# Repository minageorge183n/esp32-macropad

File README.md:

# 🔘 ESP32 Bluetooth + WiFi Macropad

A custom-built macropad featuring **9 programmable keys** and **2 rotary encoders**, designed for productivity, streaming, editing, and general automation.
It connects via **Bluetooth** for real-time input and **WiFi** for easy configuration through a web-based UI.

---

## ✨ Features

* 🎹 **9 Mechanical Keys**
  Fully programmable keys that can send:

  * Keyboard shortcuts
  * Media controls
  * Text strings

* 🔄 **2 Rotary Encoders**
  Each encoder supports:

  * Clockwise / Counterclockwise rotation
  * Push button click

* 📡 **Dual Connectivity**

  * **Bluetooth (BLE)** → Acts as a wireless keyboard
  * **WiFi** → Hosts a configuration web interface

* 🌐 **Web UI Configuration**

  * Access via browser (phone or PC)
  * Remap keys and encoders 
  * No need to reflash firmware for changes

---

## ⚙️ How It Works

### Bluetooth Mode

* The macropad connects to your device as a **BLE keyboard**
* Pressing keys sends predefined actions instantly

### WiFi Mode

* The device creates or connects to a WiFi network
* You access a **local web page** hosted on the ESP32
* From there, you can:

  * Change key mappings
  * Assign new actions
  * Save configurations

---

## 🚀 Getting Started

### 1. Power On

* Connect the macropad via USB or battery
* It will automatically start Bluetooth and WiFi services

### 2. Connect via Bluetooth

* Pair it like a normal keyboard
* Start using default key mappings

### 3. Access Web Interface

* Connect to the same WiFi network (or device hotspot mode)
* Open browser and go to:

  ```
  http://<device-ip>
  ```
* Configure keys and encoders from the UI

---

## 🧠 Key Mapping Capabilities

Each key can be configured to:

* 🔹 Send a single key (e.g., `A`, `Enter`)
* 🔹 Use modifiers (`Ctrl`, `Alt`, `Shift`)
* 🔹 Trigger media actions (volume, play/pause)
* 🔹 Type full strings (macros)

---

## 🎛️ Rotary Encoder Functions

Each encoder supports:

* ↻ Rotate Left → Action 1
* ↺ Rotate Right → Action 2
* ⏺ Press → Action 3

Example uses:

* Volume control
* Timeline scrubbing
* Zoom in/out

---

## 🛠️ Hardware Overview

* ESP32 microcontroller
* 9 mechanical switches
* 2 rotary encoders with push buttons
* Optional battery module

---

## 📌 Use Cases

* 🎥 Streaming (OBS, shortcuts)
* 🎨 Design (Photoshop, Illustrator)
* 🎬 Video editing (Premiere, DaVinci)
* 💻 General productivity
* 🎮 Gaming macros

---

## 🔮 Future Improvements

* Profiles switching
* OLED display support
* Cloud sync for configs
* Mobile app companion

---

## 📄 Notes

* Make sure Bluetooth is enabled on your device
* Web UI works best on modern browsers
* Keep firmware updated for new features

---

## 🤝 Contributing

This is a personal project, but ideas and improvements are always welcome.

---

## 📜 License

---

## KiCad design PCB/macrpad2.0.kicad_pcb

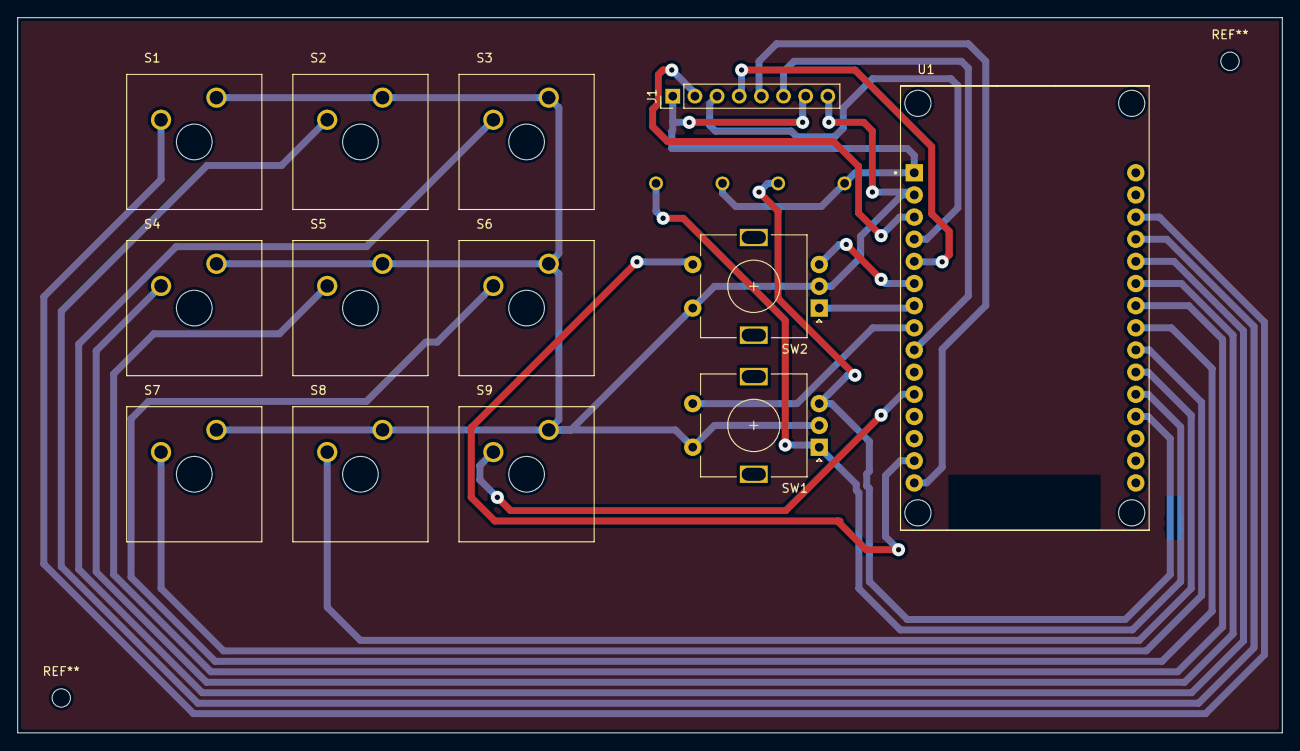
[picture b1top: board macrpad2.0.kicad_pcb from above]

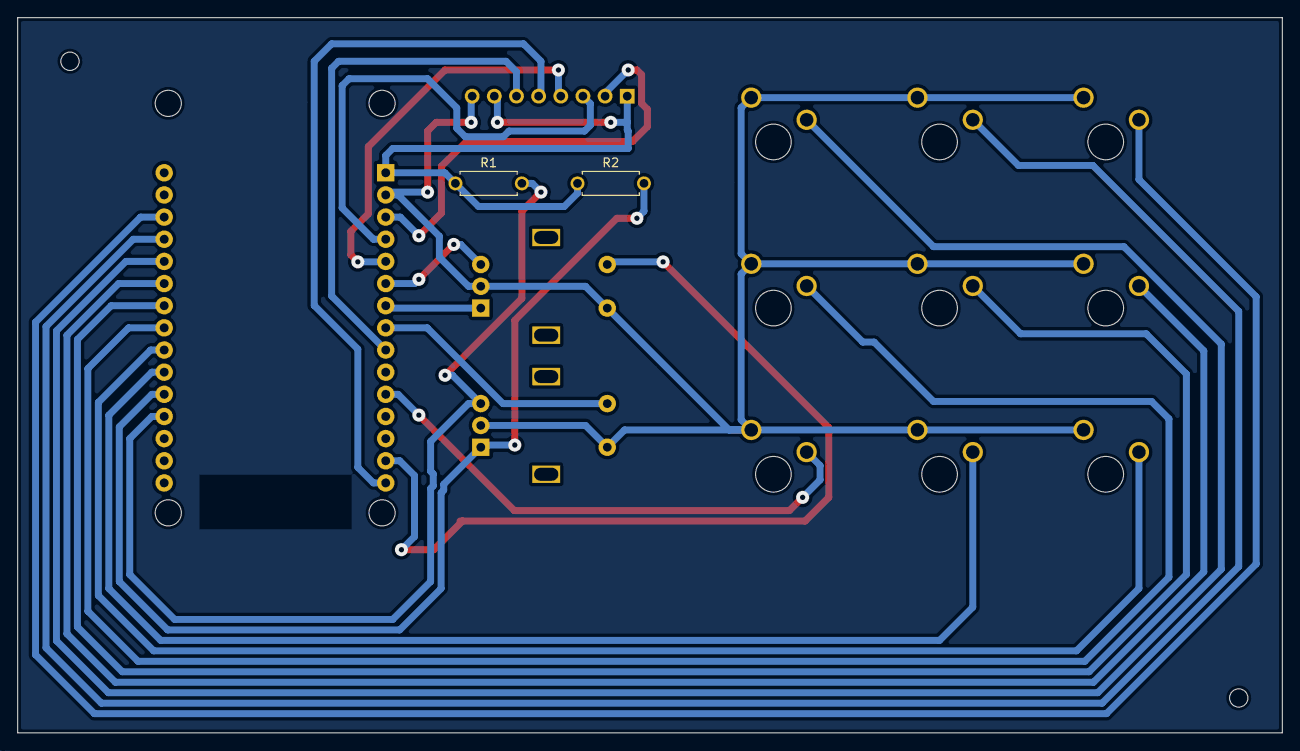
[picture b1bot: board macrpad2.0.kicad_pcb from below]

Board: 2 copper layers, 145.0 x 82.0 mm, 15 parts (2 on the bottom side), 22 nets.

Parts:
J1: Conn_01x08_Pin; PinHeader_1x08_P2.54mm_Vertical
R1, R2: Resistor; R_Axial_DIN0207_L6.3mm_D2.5mm_P7.62mm_Horizontal
S1, S2, S3, S4, S5, S6, S7, S8, S9: SW_MX1A-11NN
SW1, SW2: RotaryEncoder_Switch; RotaryEncoder_Alps_EC11E-Switch_Vertical_H20mm
U1: DEVKIT_V1_ESP32-WROOM-32; MODULE_DEVKIT_V1_ESP32-WROOM-32

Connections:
/d12: S2.1, U1.27 (D12)
/d13: S1.1, U1.28 (D13)
/d14: S3.1, U1.26 (D14)
GND: J1.8, S1.2, S2.2, S3.2, S4.2, S5.2, S6.2, S7.2, S8.2, S9.2, SW1.C, SW1.S2, SW2.C, SW2.S2, U1.2 (GND), U1.29 (GND)
unnamed: J1.1, J1.7, R1.1, R2.1, U1.1 (3V3)
unnamed: J1.2, U1.3 (D15)
unnamed: J1.3, U1.4 (D2)
unnamed: J1.4, U1.5 (D4)
unnamed: J1.5, U1.15 (D23)
unnamed: J1.6, U1.9 (D18)
unnamed: SW1.S1, U1.8 (D5)
unnamed: S9.1, U1.11 (D21)
unnamed: SW2.S1, U1.14 (D22)
unnamed: S6.1, U1.23 (D25)
unnamed: S5.1, U1.24 (D26)
unnamed: S4.1, U1.25 (D27)
unnamed: S8.1, U1.21 (D32)
unnamed: S7.1, U1.22 (D33)
unnamed: R1.2, SW1.B, U1.19 (D34)
unnamed: R2.2, SW1.A, U1.20 (D35)
unnamed: SW2.B, U1.6 (RX2)
unnamed: SW2.A, U1.7 (TX2)

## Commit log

2026-06-03 Add keymap definitions for media and dev tools
    Define key mappings and actions for different modes.
2026-06-03 Add main.cpp for Macropad functionality
2026-06-03 Revise README with features and setup instructions
    Expanded README to include detailed features, usage instructions, and future improvements for the ESP32 Macropad project.
2026-06-25 Add files via upload
    gerber files without Plated through holes (using via's instead )
2026-06-25 Add files via upload
    gerber files
2026-06-25 Add files via upload
    kicad files
